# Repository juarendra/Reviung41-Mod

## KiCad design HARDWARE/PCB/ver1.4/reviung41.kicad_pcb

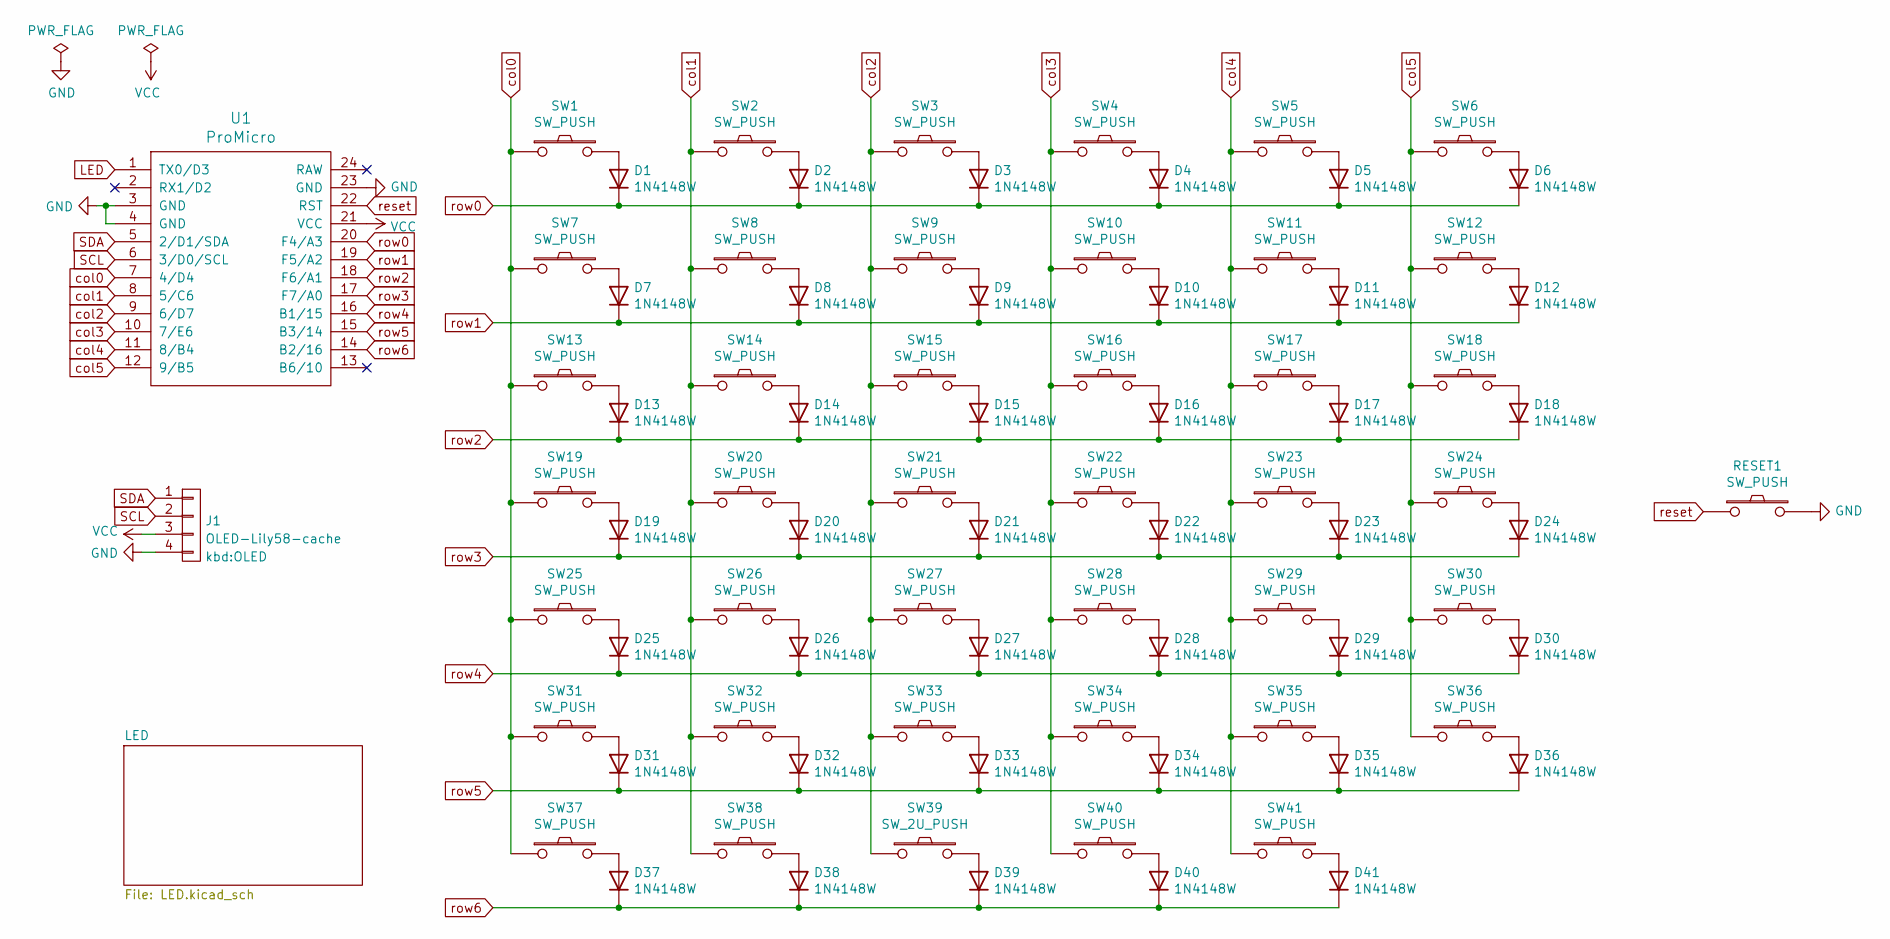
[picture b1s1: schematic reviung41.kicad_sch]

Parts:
D1, D2, D3, D4, D5, D6, D7, D8, D9, D10, D11, D12, D13, D14, D15, D16, D17, D18, D19, D20, D21, D22, D23, D24, D25, D26, D27, D28, D29, D30, D31, D32, D33, D34, D35, D36, D37, D38, D39, D40, D41: 1N4148W; D3_SMD_1side
J1: OLED-Lily58-cache; OLED
RESET1: SW_PUSH; ResetSW_1side
SW1, SW2, SW3, SW4, SW5, SW6, SW7, SW8, SW9, SW10, SW11, SW12, SW13, SW14, SW15, SW16, SW17, SW18, SW19, SW20, SW21, SW22, SW23, SW24, SW25, SW26, SW27, SW28, SW29, SW30, SW31, SW32, SW33, SW34, SW35, SW36, SW37, SW38, SW40, SW41: SW_PUSH; MXOnly-1U-Hotswap
SW39: SW_2U_PUSH; MXOnly-2U-Hotswap-ReversedStabilizers
U1: ProMicro

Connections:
GND: J1.4, RESET1.2, U1.3 (GND), U1.4 (GND), U1.23 (GND); also elsewhere on the board
LED: U1.1 (TX0/D3); also elsewhere on the board
unnamed: D1.2 (A), SW1.2
unnamed: D2.2 (A), SW2.2
unnamed: D3.2 (A), SW3.2
unnamed: D4.2 (A), SW4.2
unnamed: D5.2 (A), SW5.2
unnamed: D6.2 (A), SW6.2
unnamed: D7.2 (A), SW7.2
unnamed: D8.2 (A), SW8.2
unnamed: D9.2 (A), SW9.2
unnamed: D10.2 (A), SW10.2
unnamed: D11.2 (A), SW11.2
unnamed: D12.2 (A), SW12.2
unnamed: D13.2 (A), SW13.2
unnamed: D14.2 (A), SW14.2
unnamed: D15.2 (A), SW15.2
unnamed: D16.2 (A), SW16.2
unnamed: D17.2 (A), SW17.2
unnamed: D18.2 (A), SW18.2
unnamed: D19.2 (A), SW19.2
unnamed: D20.2 (A), SW20.2
unnamed: D21.2 (A), SW21.2
unnamed: D22.2 (A), SW22.2
unnamed: D23.2 (A), SW23.2
unnamed: D24.2 (A), SW24.2
unnamed: D25.2 (A), SW25.2
unnamed: D26.2 (A), SW26.2
unnamed: D27.2 (A), SW27.2
unnamed: D28.2 (A), SW28.2
unnamed: D29.2 (A), SW29.2
unnamed: D30.2 (A), SW30.2
unnamed: D31.2 (A), SW31.2
unnamed: D32.2 (A), SW32.2
unnamed: D33.2 (A), SW33.2
unnamed: D34.2 (A), SW34.2
unnamed: D35.2 (A), SW35.2
unnamed: D36.2 (A), SW36.2
unnamed: D37.2 (A), SW37.2
unnamed: D38.2 (A), SW38.2
unnamed: D39.2 (A), SW39.2
unnamed: D40.2 (A), SW40.2
unnamed: D41.2 (A), SW41.2
SCL: J1.2, U1.6 (3/D0/SCL)
SDA: J1.1, U1.5 (2/D1/SDA)
VCC: J1.3, U1.21 (VCC); also elsewhere on the board
col0: SW1.1, SW7.1, SW13.1, SW19.1, SW25.1, SW31.1, SW37.1, U1.7 (4/D4)
col1: SW2.1, SW8.1, SW14.1, SW20.1, SW26.1, SW32.1, SW38.1, U1.8 (5/C6)
col2: SW3.1, SW9.1, SW15.1, SW21.1, SW27.1, SW33.1, SW39.1, U1.9 (6/D7)
col3: SW4.1, SW10.1, SW16.1, SW22.1, SW28.1, SW34.1, SW40.1, U1.10 (7/E6)
col4: SW5.1, SW11.1, SW17.1, SW23.1, SW29.1, SW35.1, SW41.1, U1.11 (8/B4)
col5: SW6.1, SW12.1, SW18.1, SW24.1, SW30.1, SW36.1, U1.12 (9/B5)
reset: RESET1.1, U1.22 (RST)
row0: D1.1 (K), D2.1 (K), D3.1 (K), D4.1 (K), D5.1 (K), D6.1 (K), U1.20 (F4/A3)
row1: D7.1 (K), D8.1 (K), D9.1 (K), D10.1 (K), D11.1 (K), D12.1 (K), U1.19 (F5/A2)
row2: D13.1 (K), D14.1 (K), D15.1 (K), D16.1 (K), D17.1 (K), D18.1 (K), U1.18 (F6/A1)
row3: D19.1 (K), D20.1 (K), D21.1 (K), D22.1 (K), D23.1 (K), D24.1 (K), U1.17 (F7/A0)
row4: D25.1 (K), D26.1 (K), D27.1 (K), D28.1 (K), D29.1 (K), D30.1 (K), U1.16 (B1/15)
row5: D31.1 (K), D32.1 (K), D33.1 (K), D34.1 (K), D35.1 (K), D36.1 (K), U1.15 (B3/14)
row6: D37.1 (K), D38.1 (K), D39.1 (K), D40.1 (K), D41.1 (K), U1.14 (B2/16)

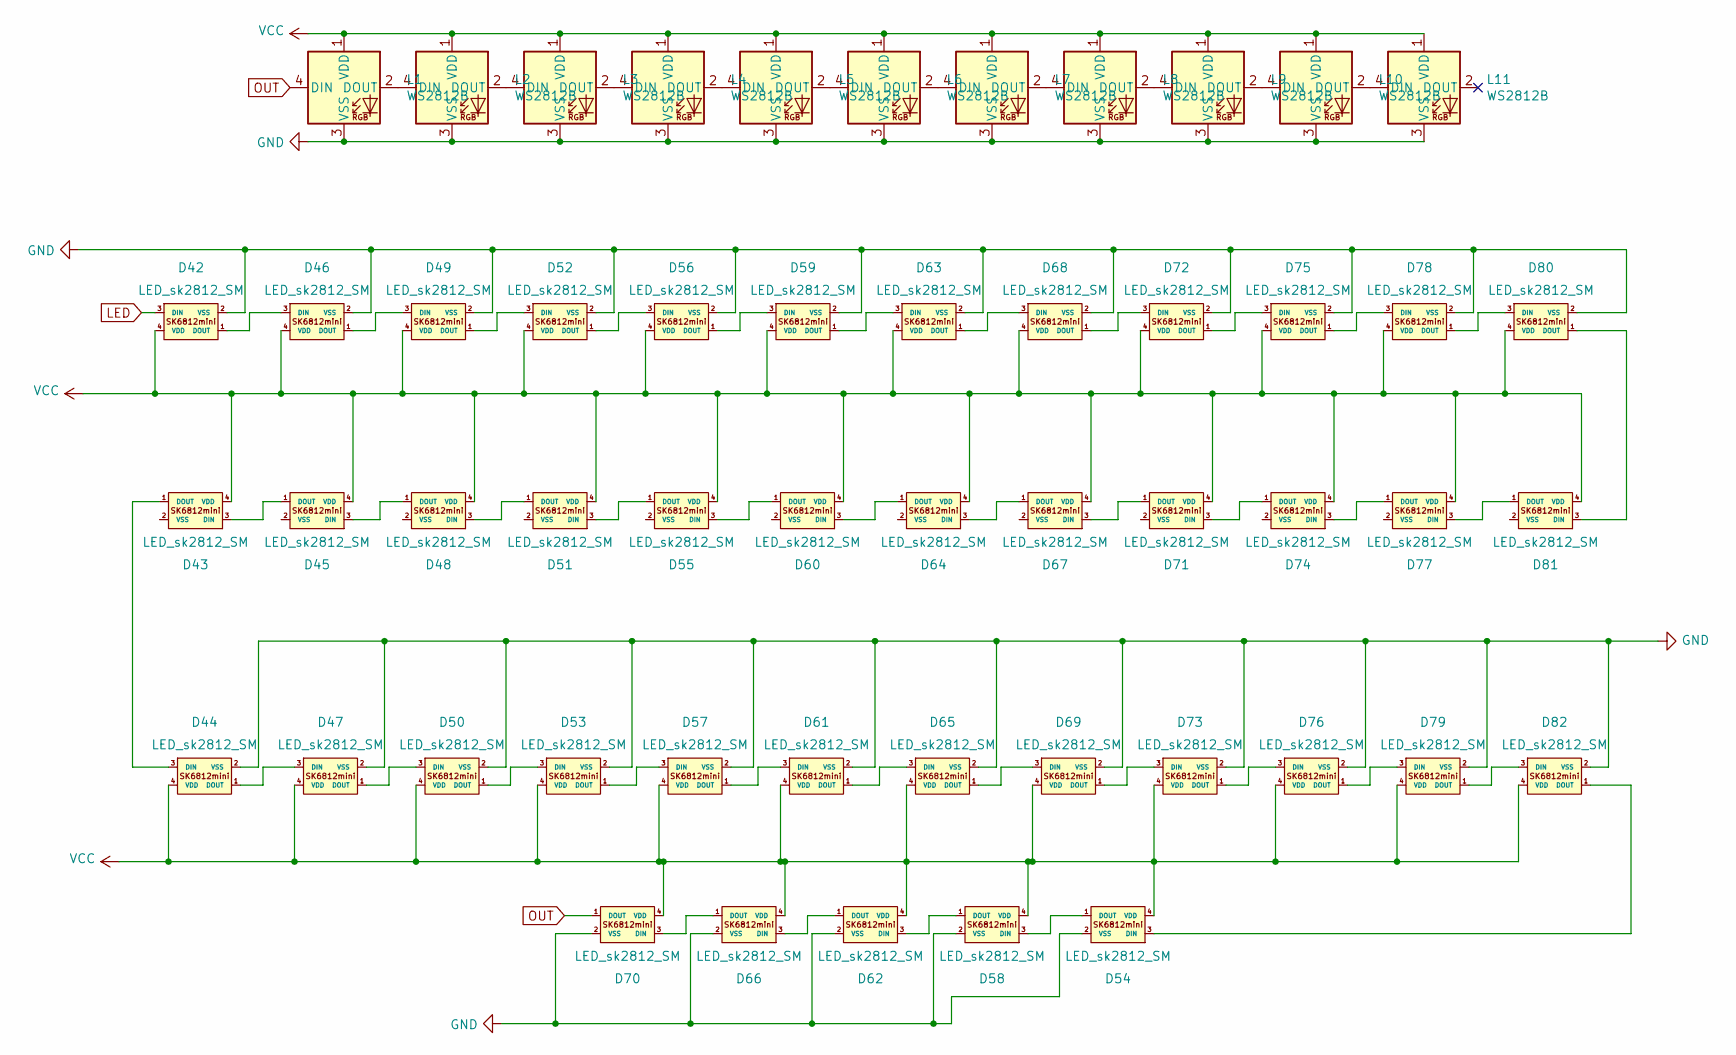
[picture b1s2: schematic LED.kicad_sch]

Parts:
D42, D43, D44, D45, D46, D47, D48, D49, D50, D51, D52, D53, D54, D55, D56, D57, D58, D59, D60, D61, D62, D63, D64, D65, D66, D67, D68, D69, D70, D71, D72, D73, D74, D75, D76, D77, D78, D79, D80, D81, D82: LED_sk2812_SM; SK6812MINI_and_cherry
L1, L2, L3, L4, L5, L6, L7, L8, L9, L10, L11: WS2812B; LED_WS2812B_PLCC4_5.0x5.0mm_P3.2mm

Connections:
GND: D42.2 (VSS), D44.2 (VSS), D46.2 (VSS), D47.2 (VSS), D49.2 (VSS), D50.2 (VSS), D52.2 (VSS), D53.2 (VSS), D54.2 (VSS), D56.2 (VSS), D57.2 (VSS), D58.2 (VSS), D59.2 (VSS), D61.2 (VSS), D62.2 (VSS), D63.2 (VSS), D65.2 (VSS), D66.2 (VSS), D68.2 (VSS), D69.2 (VSS), D70.2 (VSS), D72.2 (VSS), D73.2 (VSS), D75.2 (VSS), D76.2 (VSS), D78.2 (VSS), D79.2 (VSS), D80.2 (VSS), D82.2 (VSS), L1.3 (VSS), L2.3 (VSS), L3.3 (VSS), L4.3 (VSS), L5.3 (VSS), L6.3 (VSS), L7.3 (VSS), L8.3 (VSS), L9.3 (VSS), L10.3 (VSS), L11.3 (VSS); also elsewhere on the board
LED: D42.3 (DIN); also elsewhere on the board
unnamed: D42.1 (DOUT), D46.3 (DIN)
unnamed: D43.3 (DIN), D45.1 (DOUT)
unnamed: D43.1 (DOUT), D44.3 (DIN)
unnamed: D44.1 (DOUT), D47.3 (DIN)
unnamed: D45.3 (DIN), D48.1 (DOUT)
unnamed: D46.1 (DOUT), D49.3 (DIN)
unnamed: D47.1 (DOUT), D50.3 (DIN)
unnamed: D48.3 (DIN), D51.1 (DOUT)
unnamed: D49.1 (DOUT), D52.3 (DIN)
unnamed: D50.1 (DOUT), D53.3 (DIN)
unnamed: D51.3 (DIN), D55.1 (DOUT)
unnamed: D52.1 (DOUT), D56.3 (DIN)
unnamed: D53.1 (DOUT), D57.3 (DIN)
unnamed: D54.3 (DIN), D82.1 (DOUT)
unnamed: D54.1 (DOUT), D58.3 (DIN)
unnamed: D55.3 (DIN), D60.1 (DOUT)
unnamed: D56.1 (DOUT), D59.3 (DIN)
unnamed: D57.1 (DOUT), D61.3 (DIN)
unnamed: D58.1 (DOUT), D62.3 (DIN)
unnamed: D59.1 (DOUT), D63.3 (DIN)
unnamed: D60.3 (DIN), D64.1 (DOUT)
unnamed: D61.1 (DOUT), D65.3 (DIN)
unnamed: D62.1 (DOUT), D66.3 (DIN)
unnamed: D63.1 (DOUT), D68.3 (DIN)
unnamed: D64.3 (DIN), D67.1 (DOUT)
unnamed: D65.1 (DOUT), D69.3 (DIN)
unnamed: D66.1 (DOUT), D70.3 (DIN)
unnamed: D67.3 (DIN), D71.1 (DOUT)
unnamed: D68.1 (DOUT), D72.3 (DIN)
unnamed: D69.1 (DOUT), D73.3 (DIN)
unnamed: D71.3 (DIN), D74.1 (DOUT)
unnamed: D72.1 (DOUT), D75.3 (DIN)
unnamed: D73.1 (DOUT), D76.3 (DIN)
unnamed: D74.3 (DIN), D77.1 (DOUT)
unnamed: D75.1 (DOUT), D78.3 (DIN)
unnamed: D76.1 (DOUT), D79.3 (DIN)
unnamed: D77.3 (DIN), D81.1 (DOUT)
unnamed: D78.1 (DOUT), D80.3 (DIN)
unnamed: D79.1 (DOUT), D82.3 (DIN)
unnamed: D80.1 (DOUT), D81.3 (DIN)
unnamed: L1.2 (DOUT), L2.4 (DIN)
unnamed: L2.2 (DOUT), L3.4 (DIN)
unnamed: L3.2 (DOUT), L4.4 (DIN)
unnamed: L4.2 (DOUT), L5.4 (DIN)
unnamed: L5.2 (DOUT), L6.4 (DIN)
unnamed: L6.2 (DOUT), L7.4 (DIN)
unnamed: L7.2 (DOUT), L8.4 (DIN)
unnamed: L8.2 (DOUT), L9.4 (DIN)
unnamed: L9.2 (DOUT), L10.4 (DIN)
unnamed: L10.2 (DOUT), L11.4 (DIN)
OUT: D70.1 (DOUT), L1.4 (DIN)
VCC: D42.4 (VDD), D43.4 (VDD), D44.4 (VDD), D45.4 (VDD), D46.4 (VDD), D47.4 (VDD), D48.4 (VDD), D49.4 (VDD), D50.4 (VDD), D51.4 (VDD), D52.4 (VDD), D53.4 (VDD), D54.4 (VDD), D55.4 (VDD), D56.4 (VDD), D57.4 (VDD), D58.4 (VDD), D59.4 (VDD), D60.4 (VDD), D61.4 (VDD), D62.4 (VDD), D63.4 (VDD), D64.4 (VDD), D65.4 (VDD), D66.4 (VDD), D67.4 (VDD), D68.4 (VDD), D69.4 (VDD), D70.4 (VDD), D71.4 (VDD), D72.4 (VDD), D73.4 (VDD), D74.4 (VDD), D75.4 (VDD), D76.4 (VDD), D77.4 (VDD), D78.4 (VDD), D79.4 (VDD), D80.4 (VDD), D81.4 (VDD), D82.4 (VDD), L1.1 (VDD), L2.1 (VDD), L3.1 (VDD), L4.1 (VDD), L5.1 (VDD), L6.1 (VDD), L7.1 (VDD), L8.1 (VDD), L9.1 (VDD), L10.1 (VDD), L11.1 (VDD); also elsewhere on the board

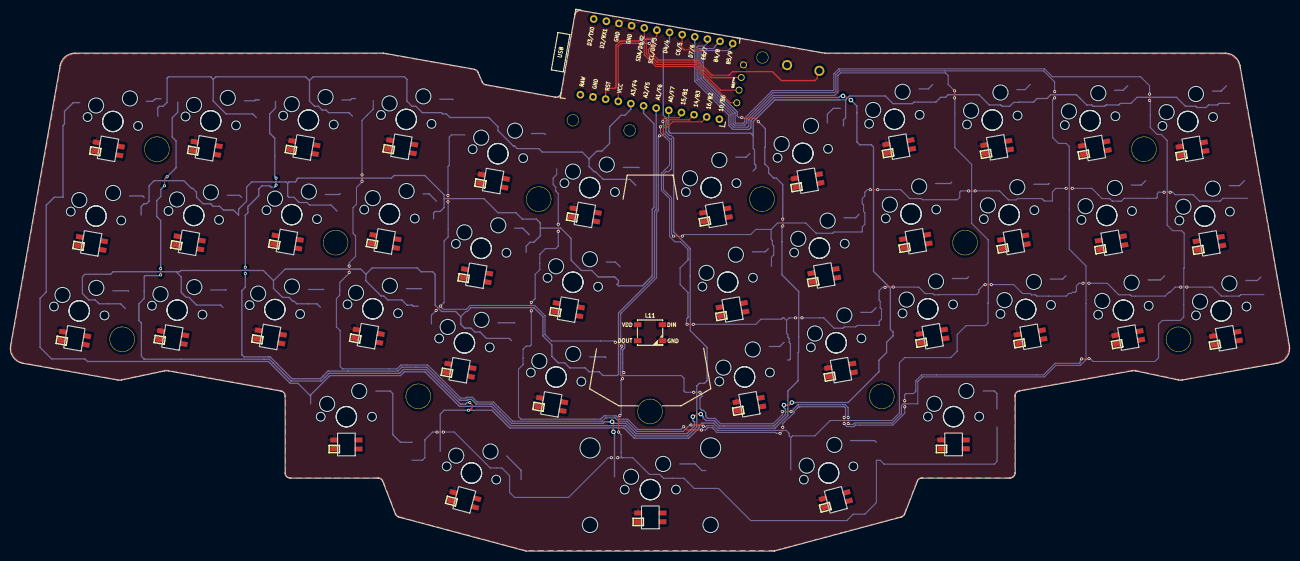
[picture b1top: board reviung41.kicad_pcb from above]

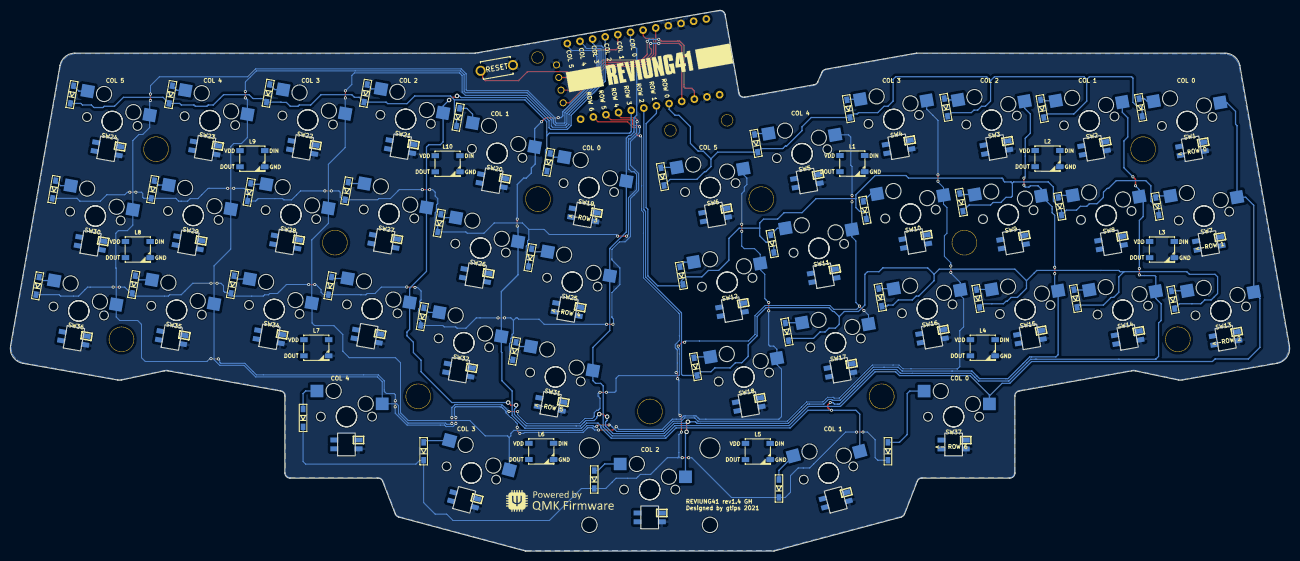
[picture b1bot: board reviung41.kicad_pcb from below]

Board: 2 copper layers, 253.3 x 107.1 mm, 151 parts (52 on the bottom side), 111 nets.

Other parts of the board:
H1: H1; HOLE
H2: H2; HOLE
H3: H3; HOLE
H4: H4; HOLE
H5: H5; HOLE
H6: H6; HOLE
H7: H7; HOLE
H8: H8; HOLE
H9: H9; HOLE
H10: H10; HOLE
H11: H11; HOLE
H12: H12; HOLE_2.2mm
H13: H13; HOLE_2.2mm
H14: H14; HOLE_2.2mm

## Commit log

2025-01-05 FEAT: re wiring switch
2025-01-06 FEAT: re wiring OLED and Reset Button
2025-01-07 FEAT: re wiring led rgb per key
2025-01-08 FEAT: add switch, connector battery and create gerber
2025-01-08 FEAT: add selector for underglow or matrix
2025-01-10 FEAT: add 3d Model
2025-01-17 FEAT: add Case 3D file and Image of rendering
2025-01-22 DOC: add privew hardware
